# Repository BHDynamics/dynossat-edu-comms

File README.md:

# DynOSSAT-EDU-Comms (Communications System)
DynOSSAT-EDU is the first open source PocketQube educational kit compatible with CircuitPython and Arduino.

This plaform is equipped with all the necessary modules for the operation of a nanosatellite (PocketQube)
in Low Earth Orbit (LEO) that would serve as a device for teaching, training, and driving curiosity about the philosophy and technology related to NewSpace.

This repository contains the hardware files for the Communications system, the module responsible for handling radio communications.It integrates a long range LoRa module
to simulate LEO-Earth communications and a 2.4 GHz nRF52832 SoC to simulate LEO-LEO communications and to allow communication with mobile apps for teaching and simulation projects using Smartphones.

Hardware in this repository is licenced under **CERN OHL v1.2**.

## Technical details

- Based on HopeRF’s RFM96W 868 MHz LoRa module, pad-to-pad compatible with the 433 MHz RFM95W version
- Easily controlled through SPI bus
- Secondary 2.4 GHz SoC (SKB369) based on Nordic Semi nRF52832 that can act as an independent or redundant processor through I2C or SPI
- Female USB-C 2.0 connector for power and data logging (CH340E USB to UART bridge)

## Documentation

Available soon!

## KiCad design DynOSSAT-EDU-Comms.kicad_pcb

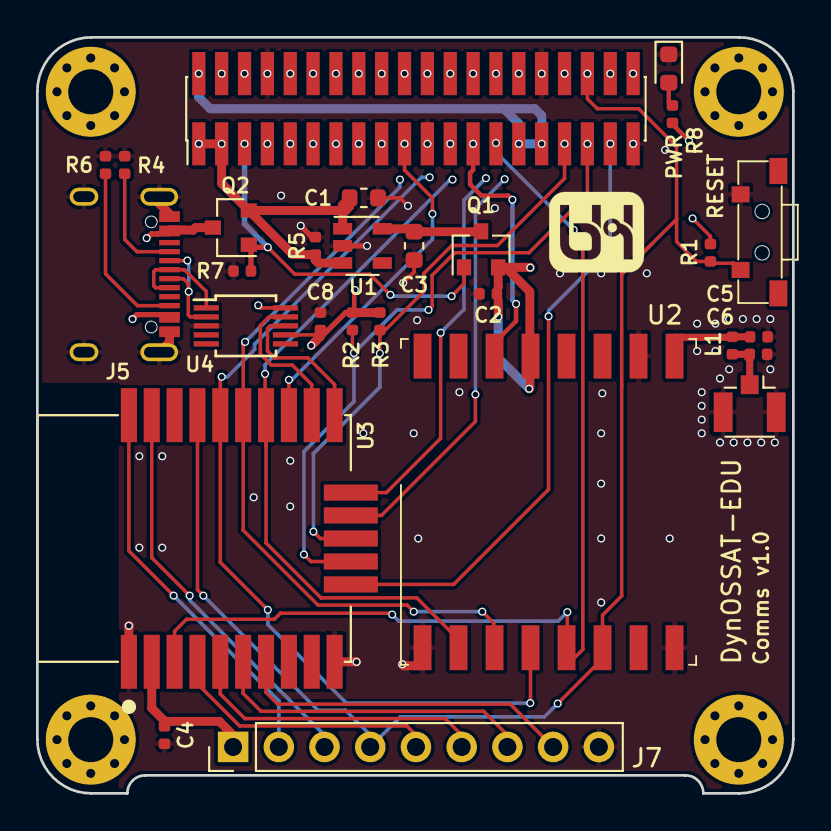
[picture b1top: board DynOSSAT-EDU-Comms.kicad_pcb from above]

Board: 4 copper layers, 42.0 x 42.0 mm, 33 parts (1 on the bottom side), 50 nets.

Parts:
C1, C3: 10uF; C_0603_1608Metric
C2, C4, C8: 100nF; C_0402_1005Metric
C5, C6: DNP; C_0402_1005Metric
D1: LED; LED_0603_1608Metric
H1, H2, H3, H4: MountingHole_Pad; MountingHole_2.5mm_Pad_Via
J1: Conn_02x20_Odd_Even; PinHeader_2x20_P1.27mm_Vertical_SMD
J2: Conn_02x20_Odd_Even; PinSocket_2x20_P1.27mm_Vertical_SMD
J4: Conn_Coaxial; U.FL_Hirose_U.FL-R-SMT-1_Vertical
J5: USB_C_Receptacle_USB2.0; U262-161N-4BVC11
J7: Conn_01x09_Female; PinHeader_1x09_P2.54mm_Vertical
L1: 0R; L_0402_1005Metric
Q1, Q2: DMG2305L; SOT-23
R1, R5, R7: 100k; R_0402_1005Metric
R2, R3: 47k; R_0402_1005Metric
R4, R6: 5.1k; R_0402_1005Metric
R8: 510R; R_0402_1005Metric
SW1: SW_Push; 1TS002G-1800-3500-CT
U1: ME6211C33; SOT-23-5
U2: RFM96; HOPERF_RFM69HW
U3: SKB369; SKYLAB_SKB369
U4: CH340E; MSOP-10_3x3mm_P0.5mm

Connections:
+3V3_SAT: C2.1, C4.1, C8.1, J1.2, J1.4, J1.29, J1.31, J2.2, J2.4, J2.29, J2.31, J7.1, Q1.2, R1.1, R2.1, R3.1, R8.1, U2.13, U3.2, U4.7, U4.10
+5V_SAT: C1.1, J1.1, J1.3, J2.1, J2.3, Q2.2, R5.1, U1.1, U1.3
/A0_OBC: J1.10, J2.10
/A1_OBC: J1.12, J2.12
/A2_OBC: J1.14, J2.14
/A3_OBC: J1.16, J2.16
/A4_OBC: J1.18, J2.18
/A5_OBC: J1.20, J2.20
/AREF: J1.6, J2.6
/D0_OBC: J1.9, J2.9
/D1_OBC: J1.11, J2.11
/D2_OBC: J1.13, J2.13
/D3_OBC: J1.15, J2.15
/D4_OBC: J1.17, J2.17
/D5_OBC: J1.19, J2.19, U3.18
/D6_OBC: J1.23, J2.23
/D7_OBC: J1.25, J2.25, U2.14
/D8_OBC: J1.27, J2.27, U2.5, U3.3
/D9_OBC: J1.37, J2.37, U3.11
/I2C_BUS_SCL: J1.35, J2.35, R2.2, U3.12
/I2C_BUS_SDA: J1.33, J2.33, R3.2, U3.13
/INT_IMU_OBC: J1.7, J2.7
/OBC_D30: J1.28, J2.28, U3.15
/OBC_D31: J1.30, J2.30, U3.14
/OBC_OVTEMP: J1.34, J2.34
/P0.26: J7.5, U3.4
/P0.27: J7.6, U3.5
/P0.28: J7.7, U3.6
/P0.29: J7.8, U3.7
/SAT_PWR_EN: J1.5, J2.5, Q1.1, Q2.1, R7.1
/SPI_BUS_SCK: J1.24, J2.24, U2.4, U3.21
/SPI_BUS_SDI: J1.26, J2.26, U2.2, U3.19
/SPI_BUS_SDO: J1.22, J2.22, U2.3, U3.20
/SWCLK: J1.38, J2.38
/SWDIO: J1.40, J2.40
/USB_D+: J5.A6, J5.B6, U4.1
/USB_D-: J5.A7, J5.B7, U4.2
/nRF_RX: U3.16, U4.8
/nRF_SWDCLK: J7.3, U3.24
/nRF_SWDIO: J7.2, U3.25
/nRF_TX: U3.17, U4.9
/nRST: J1.36, J2.36, J7.4, R1.2, SW1.1, U2.6, U3.22
GND: C1.2, C2.2, C3.2, C4.2, C5.2, C6.2, C8.2, D1.1, J1.8, J1.21, J1.32, J1.39, J2.8, J2.21, J2.32, J2.39, J4.2, J5.A1, J5.A12, J5.B1, J5.B12, J5.S1, J7.9, R4.1, R5.2, R6.1, R7.2, SW1.2, U1.2, U2.1, U2.8, U2.10, U3.1, U3.10, U4.3
unnamed: C3.1, Q1.3, U1.5
unnamed: C5.1, L1.1, U2.9
unnamed: C6.1, J4.1, L1.2
unnamed: D1.2, R8.2
unnamed: J5.A5, R4.2
unnamed: J5.B5, R6.2
VBUS: J5.A4, J5.A9, J5.B4, J5.B9, Q2.3

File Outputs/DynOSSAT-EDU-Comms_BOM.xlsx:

Item | Qty | Reference(s) | Value | Part Number | Footprint
1 | 2 | C1, C3 | 10uF |  | 0603 10uF X7R/X5R 10V or greater
2 | 3 | C2, C4, C8 | 100nF |  | 0402 100nF X7R/X5R 10V or greater
3 | 2 | C5, C6 | DNP | -
4 | 1 | D1 | LED | Device:LED | 0603 LED Red
5 | 1 | J1 | Main Bus PQBH40 | We don't have part numbers. Use generic connectors | Pin header male 1.27mm pitch 2x20 vertical SMD
6 | 1 | J2 | Main Bus PQBH40 | We don't have part numbers. Use generic connectors | Pin socket female 1.27mm pitch 2x20 vertical SMD
7 | 1 | J4 | Conn_Coaxial | U.FL-R-SMT-1(80) | 50 ohm U.FL Coaxial Connector
8 | 1 | J5 | USB_C_Receptacle_USB2.0 | U262-161N-4BVC11 | USB-C 2.0 connector - female socket
9 | 1 | J7 | Conn_01x09_Female | We don't have part numbers. Use generic connectors | Pin header male 2.54mm pitch 1x09 vertican Through Hole
10 | 1 | L1 | 0R |  | 0 ohm resistor 0402
11 | 2 | Q1, Q2 | DMG2305L | DMG2305UX-7 | P-Channel Power Mosfet
12 | 3 | R1, R5, R7 | 100k |  | 0402 100k 1%
13 | 2 | R2, R3 | 47k |  | 0402 47k 1%
14 | 2 | R4, R6 | 5.1k |  | 0402 5.1k 1%
15 | 1 | R8 | 510R |  | 0402 510R 1%
16 | 1 | SW1 | SW_Push | 1TS002G-1800-3500-CT | Push Button side mount
17 | 1 | U1 | ME6211C33 | ME6211C33M5G-N | 3V3 LDO SOT-23-5
18 | 1 | U2 | HopeRF RFM95 | RFM95W | 868 MHz LoRA module - global version
19 | 1 | U3 | Skylab SKB369 | SKB369 | Bluetooth Low Energy Module
20 | 1 | U4 | CH340E | CH340E | USB to UART Bridge IC SOIC-8
For passives (resistors, capacitors, etc) you may use any quality brand while m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

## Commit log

2020-10-15 First commit, v1.0 RC
2020-10-16 Add README and LICENCE
2020-11-06 Replace MISO/MOSI for SDI/SDO
    Update library to latest version
